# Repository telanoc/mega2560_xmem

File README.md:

# mega2560_xmem
A slight reworking of Andy Brown's external SRAM expansion for the Arduino
Mega 2560

Andy's site, which has software and programming examples and whatnot:

    http://andybrown.me.uk

Link to the Osh Park shared project I made for the very first
version of this I did:

	https://www.oshpark.com/shared_projects/5dhn3IBO

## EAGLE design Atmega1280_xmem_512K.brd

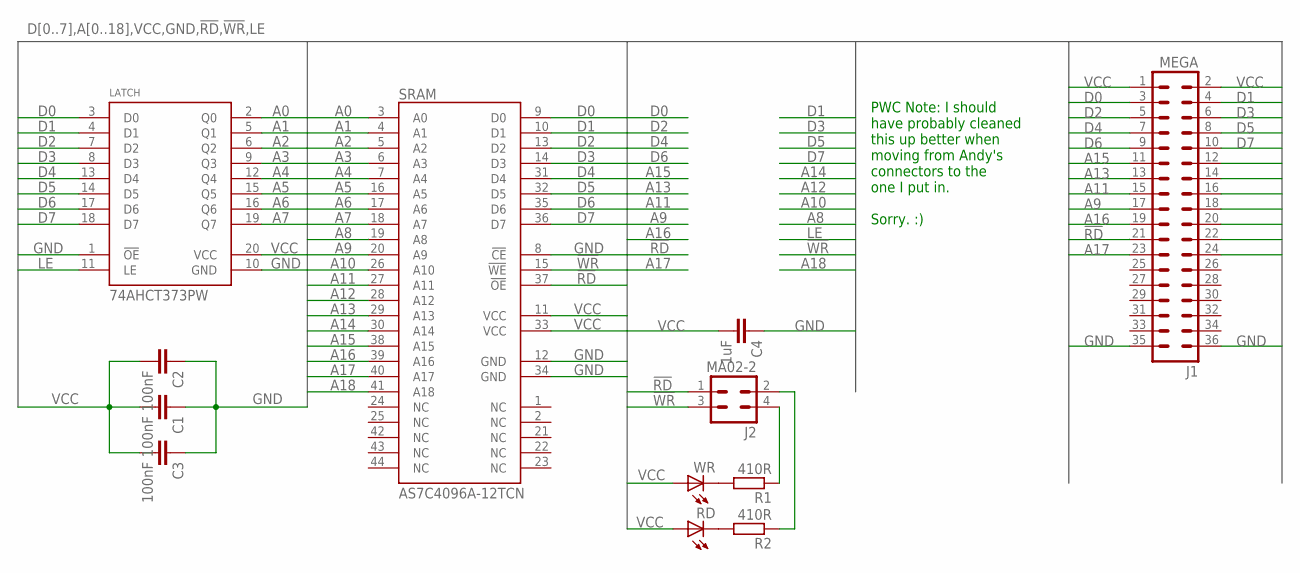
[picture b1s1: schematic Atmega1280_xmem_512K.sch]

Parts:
C1, C2, C3: 100nF; C0603
C4: 1uF; C0603
J1: MEGA; MA18-2
J2: MA02-2
LATCH: 74AHCT373PW; TSSOP20
R1, R2: 410R; R0805
RD: LEDSMT1206; 1206
SRAM: AS7C4096A-12TCN; TSOP44-II
WR: LEDSMT1206; 1206

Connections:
!RD: J1.21, J2.1, SRAM.37 (!OE)
!WR: J1.22, J2.3, SRAM.15 (!WE)
A0: LATCH.2 (Q0), SRAM.3 (A0)
A1: LATCH.5 (Q1), SRAM.4 (A1)
A2: LATCH.6 (Q2), SRAM.5 (A2)
A3: LATCH.9 (Q3), SRAM.6 (A3)
A4: LATCH.12 (Q4), SRAM.7 (A4)
A5: LATCH.15 (Q5), SRAM.16 (A5)
A6: LATCH.16 (Q6), SRAM.17 (A6)
A7: LATCH.19 (Q7), SRAM.18 (A7)
A8: J1.18, SRAM.19 (A8)
A9: J1.17, SRAM.20 (A9)
A10: J1.16, SRAM.26 (A10)
A11: J1.15, SRAM.27 (A11)
A12: J1.14, SRAM.28 (A12)
A13: J1.13, SRAM.29 (A13)
A14: J1.12, SRAM.30 (A14)
A15: J1.11, SRAM.38 (A15)
A16: J1.19, SRAM.39 (A16)
A17: J1.23, SRAM.40 (A17)
A18: J1.24, SRAM.41 (A18)
D0: J1.3, LATCH.3 (D0), SRAM.9 (D0)
D1: J1.4, LATCH.4 (D1), SRAM.10 (D1)
D2: J1.5, LATCH.7 (D2), SRAM.13 (D2)
D3: J1.6, LATCH.8 (D3), SRAM.14 (D3)
D4: J1.7, LATCH.13 (D4), SRAM.31 (D4)
D5: J1.8, LATCH.14 (D5), SRAM.32 (D5)
D6: J1.9, LATCH.17 (D6), SRAM.35 (D6)
D7: J1.10, LATCH.18 (D7), SRAM.36 (D7)
GND: C1.1, C2.1, C3.1, C4.1, J1.35, J1.36, LATCH.1 (!OE), LATCH.10 (GND), SRAM.8 (!CE), SRAM.12 (GND), SRAM.34 (GND)
LE: J1.20, LATCH.11 (LE)
unnamed: J2.4, R1.1
unnamed: J2.2, R2.1
unnamed: R2.2, RD.C
unnamed: R1.2, WR.C
VCC: C1.2, C2.2, C3.2, C4.2, J1.1, J1.2, LATCH.20 (VCC), RD.A, SRAM.11 (VCC), SRAM.33 (VCC), WR.A

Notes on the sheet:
PWC Note: I should have probably cleaned this up better when moving from Andy's connectors to the one I put in. Sorry. :)

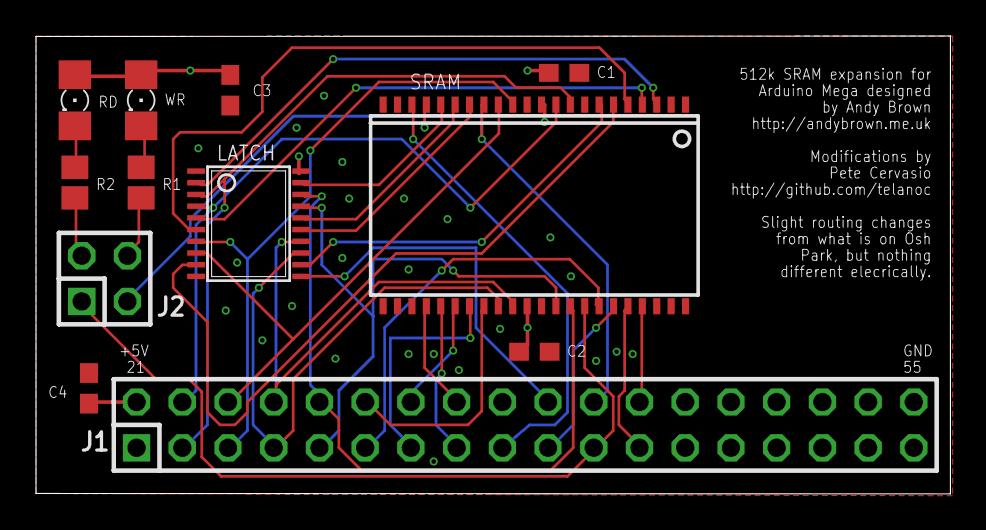
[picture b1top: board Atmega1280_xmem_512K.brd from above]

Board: 4 copper layers, 50.8 x 25.4 mm, 12 parts (0 on the bottom side), 36 nets.

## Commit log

2015-11-19 Added Eagle schematic and board
